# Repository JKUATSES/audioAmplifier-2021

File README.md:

# audioAmplifier-2021
This is a description of a simple audio amplifier design. The IC used is the TEA2025B and it is applied in bridge-tied mode for single speaker application.

<!--EQUALIZER_CIRCUITS-->
https://bestengineeringprojects.com/tone-control-circuit-active-and-passive/   <!-- primary source of LM741 equalizer/tonality control circuit -->
https://www.angelfire.com/electronic/funwithtubes/Amp-Tone-A.html
https://www.circuitstoday.com/passive-tone-control-circuit
https://learnabout-electronics.org/Amplifiers/amplifiers42.php

<!--PREAMPLIFIER_CIRCUITS-->
https://www.homemade-circuits.com/small-amplifier-circuit/
https://bestengineeringprojects.com/preamplifier-circuit/

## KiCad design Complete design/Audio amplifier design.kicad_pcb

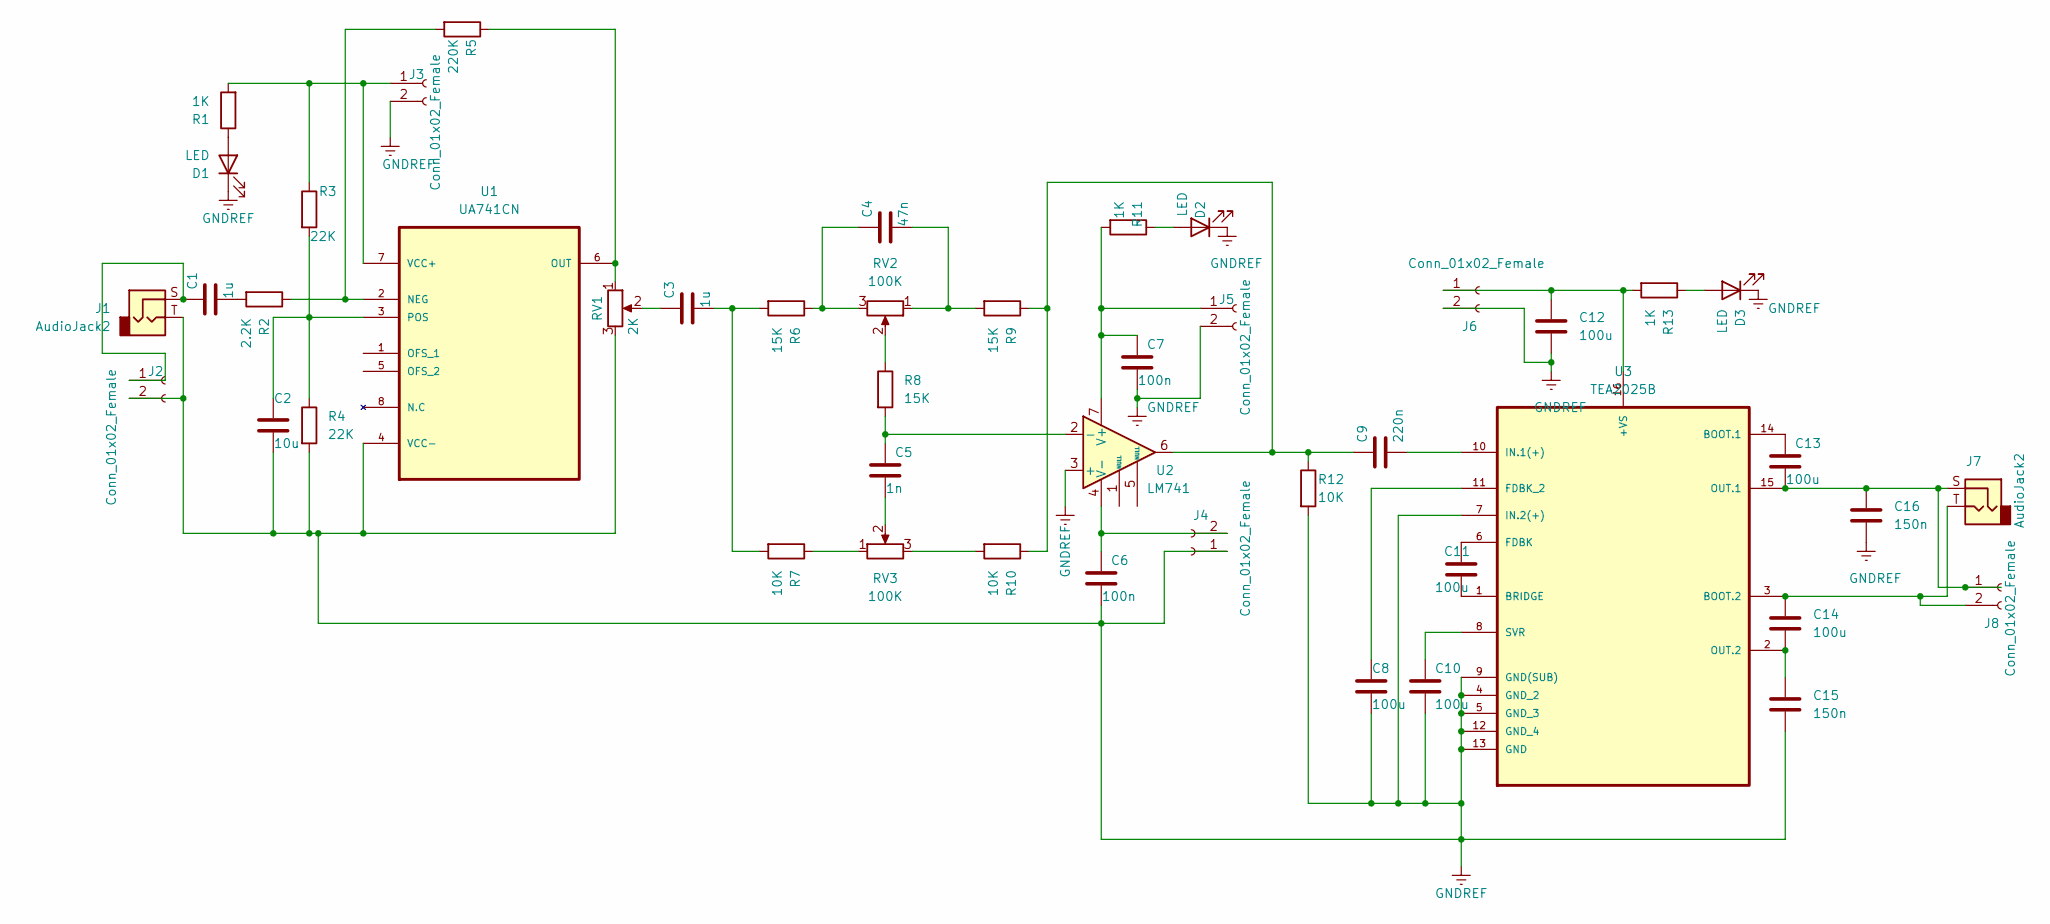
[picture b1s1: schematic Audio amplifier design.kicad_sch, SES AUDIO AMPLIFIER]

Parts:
C1, C3: 1u; CP_Radial_D5.0mm_P2.50mm
C2: 10u; CP_Radial_D5.0mm_P2.50mm
C4: 47n; CP_Radial_D5.0mm_P2.50mm
C5: 1n; CP_Radial_D5.0mm_P2.50mm
C6, C7: 100n; CP_Radial_D5.0mm_P2.50mm
C8, C10, C11, C12, C13, C14: 100u; CP_Radial_D5.0mm_P2.50mm
C9: 220n; CP_Radial_D5.0mm_P2.50mm
C15, C16: 150n; CP_Radial_D5.0mm_P2.50mm
D1, D2, D3: LED; LED_D5.0mm
J1, J7: AudioJack2; Jack_3.5mm_CUI_SJ1-3533NG_Horizontal
J2, J3, J4, J5, J6, J8: Conn_01x02_Female; TerminalBlock_4Ucon_1x02_P3.50mm_Vertical
R1, R11, R13: 1K; R_Axial_DIN0204_L3.6mm_D1.6mm_P7.62mm_Horizontal
R2: 2.2K; R_Axial_DIN0204_L3.6mm_D1.6mm_P7.62mm_Horizontal
R3, R4: 22K; R_Axial_DIN0204_L3.6mm_D1.6mm_P7.62mm_Horizontal
R5: 220K; R_Axial_DIN0204_L3.6mm_D1.6mm_P7.62mm_Horizontal
R6, R8, R9: 15K; R_Axial_DIN0204_L3.6mm_D1.6mm_P7.62mm_Horizontal
R7, R10, R12: 10K; R_Axial_DIN0204_L3.6mm_D1.6mm_P7.62mm_Horizontal
RV1: 2K; Potentiometer_ACP_CA9-H5_Horizontal
RV2, RV3: 100K; Potentiometer_ACP_CA9-H5_Horizontal
U1: UA741CN; DIP254P762X533-8; MPN UA741CN
U2: LM741; DIP254P762X533-8
U3: TEA2025B; DIP254P762X510-16; MPN TEA2025B

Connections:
GNDREF: C2.2, C6.2, C7.2, C8.2, C10.2, C12.2, C15.2, C16.2, D1.1 (K), D2.1 (K), D3.1 (K), J1.T, J2.2, J3.2, J4.1, J5.2, J6.2, R4.2, R12.2, RV1.3, U1.4 (VCC-), U2.3 (+), U3.4 (GND_2), U3.5 (GND_3), U3.7 (IN.2(+)), U3.9 (GND(SUB)), U3.12 (GND_4), U3.13 (GND)
unnamed: C1.1, J1.S, J2.1
unnamed: C1.2, R2.2
unnamed: C2.1, R3.2, R4.1, U1.3 (POS)
unnamed: C3.1, RV1.2
unnamed: C3.2, R6.2, R7.2
unnamed: C4.1, R6.1, RV2.3
unnamed: C4.2, R9.2, RV2.1
unnamed: C5.1, R8.2, U2.2 (-)
unnamed: C5.2, RV3.2
unnamed: C6.1, J4.2, U2.4 (V-)
unnamed: C7.1, J5.1, R11.2, U2.7 (V+)
unnamed: C8.1, U3.11 (FDBK_2)
unnamed: C9.1, R9.1, R10.1, R12.1, U2.6
unnamed: C9.2, U3.10 (IN.1(+))
unnamed: C10.1, U3.8 (SVR)
unnamed: C11.1, U3.6 (FDBK)
unnamed: C11.2, U3.1 (BRIDGE)
unnamed: C12.1, J6.1, R13.2, U3.16 (+VS)
unnamed: C13.1, U3.14 (BOOT.1)
unnamed: C13.2, C16.1, J7.S, J8.1, U3.15 (OUT.1)
unnamed: C14.1, J7.T, J8.2, U3.3 (BOOT.2)
unnamed: C14.2, C15.1, U3.2 (OUT.2)
unnamed: D1.2 (A), R1.1
unnamed: D2.2 (A), R11.1
unnamed: D3.2 (A), R13.1
unnamed: J3.1, R1.2, R3.1, U1.7 (VCC+)
unnamed: R2.1, R5.2, U1.2 (NEG)
unnamed: R5.1, RV1.1, U1.6 (OUT)
unnamed: R7.1, RV3.1
unnamed: R8.1, RV2.2
unnamed: R10.2, RV3.3

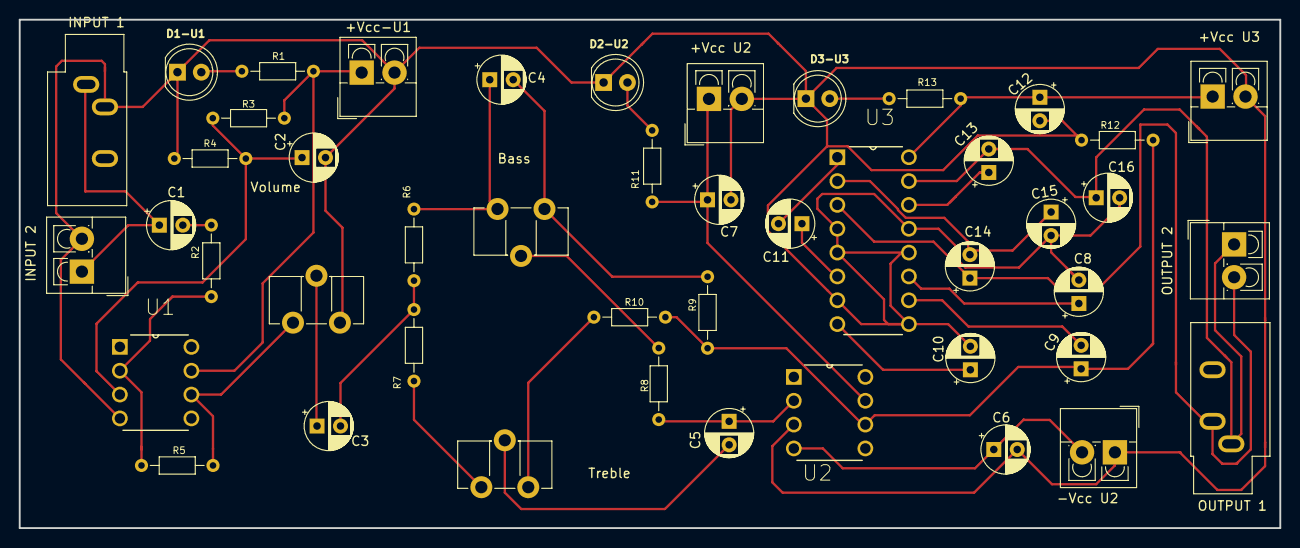
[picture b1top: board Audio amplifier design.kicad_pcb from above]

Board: 2 copper layers, 134.3 x 54.2 mm, 46 parts (0 on the bottom side), 32 nets.

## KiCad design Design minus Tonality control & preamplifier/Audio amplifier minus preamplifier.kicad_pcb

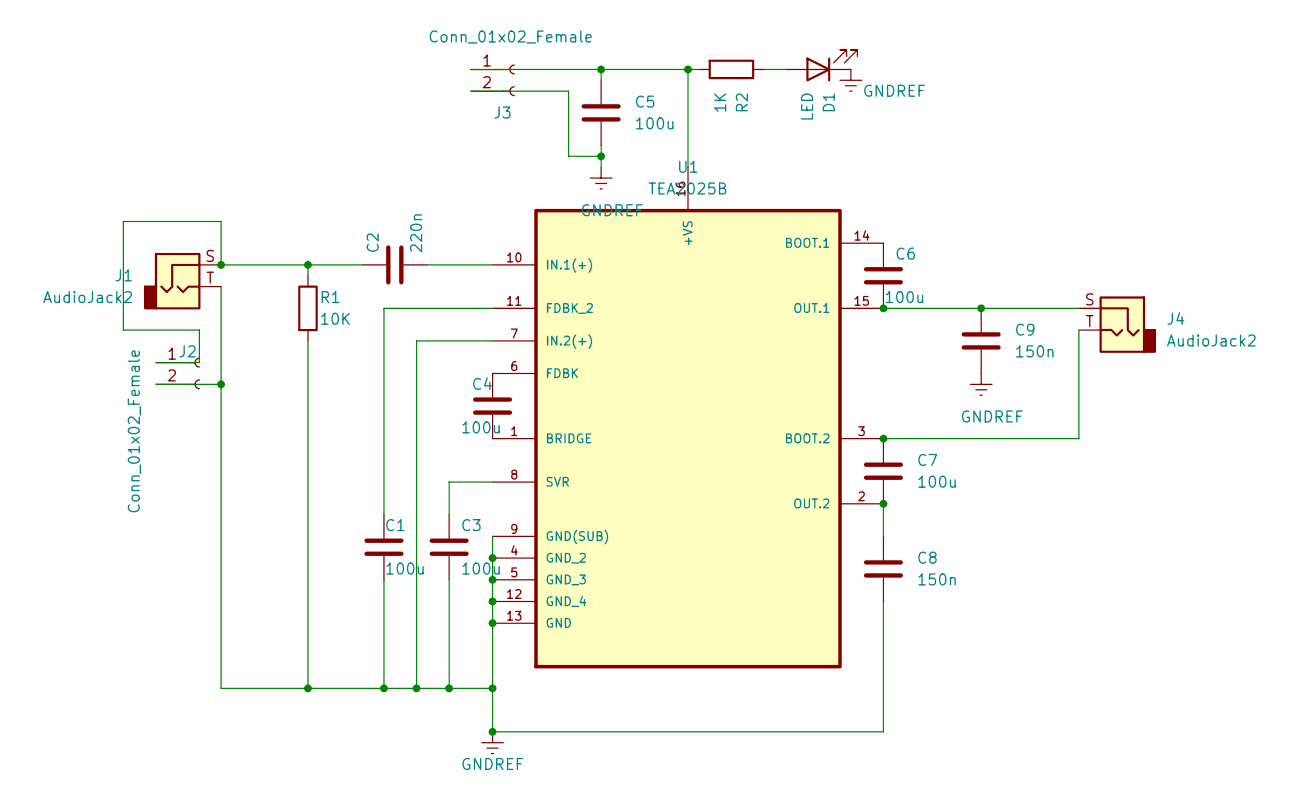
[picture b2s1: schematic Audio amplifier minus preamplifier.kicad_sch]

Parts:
C1, C3, C4, C5, C6, C7: 100u; CP_Radial_D5.0mm_P2.50mm
C2: 220n; CP_Radial_D5.0mm_P2.50mm
C8, C9: 150n; CP_Radial_D5.0mm_P2.50mm
D1: LED; LED_D5.0mm
J1, J4: AudioJack2; Jack_3.5mm_CUI_SJ-3523-SMT_Horizontal
J2, J3: Conn_01x02_Female; TerminalBlock_4Ucon_1x02_P3.50mm_Vertical
R1: 10K; R_Axial_DIN0204_L3.6mm_D1.6mm_P7.62mm_Horizontal
R2: 1K; R_Axial_DIN0204_L3.6mm_D1.6mm_P7.62mm_Horizontal
U1: TEA2025B; DIP254P762X510-16; MPN TEA2025B

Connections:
GNDREF: C1.2, C3.2, C5.2, C8.2, C9.2, D1.1 (K), J1.T, J2.2, J3.2, R1.2, U1.4 (GND_2), U1.5 (GND_3), U1.7 (IN.2(+)), U1.9 (GND(SUB)), U1.12 (GND_4), U1.13 (GND)
unnamed: C1.1, U1.11 (FDBK_2)
unnamed: C2.1, J1.S, J2.1, R1.1
unnamed: C2.2, U1.10 (IN.1(+))
unnamed: C3.1, U1.8 (SVR)
unnamed: C4.1, U1.6 (FDBK)
unnamed: C4.2, U1.1 (BRIDGE)
unnamed: C5.1, J3.1, R2.2, U1.16 (+VS)
unnamed: C6.1, U1.14 (BOOT.1)
unnamed: C6.2, C9.1, J4.S, U1.15 (OUT.1)
unnamed: C7.1, J4.T, U1.3 (BOOT.2)
unnamed: C7.2, C8.1, U1.2 (OUT.2)
unnamed: D1.2 (A), R2.1

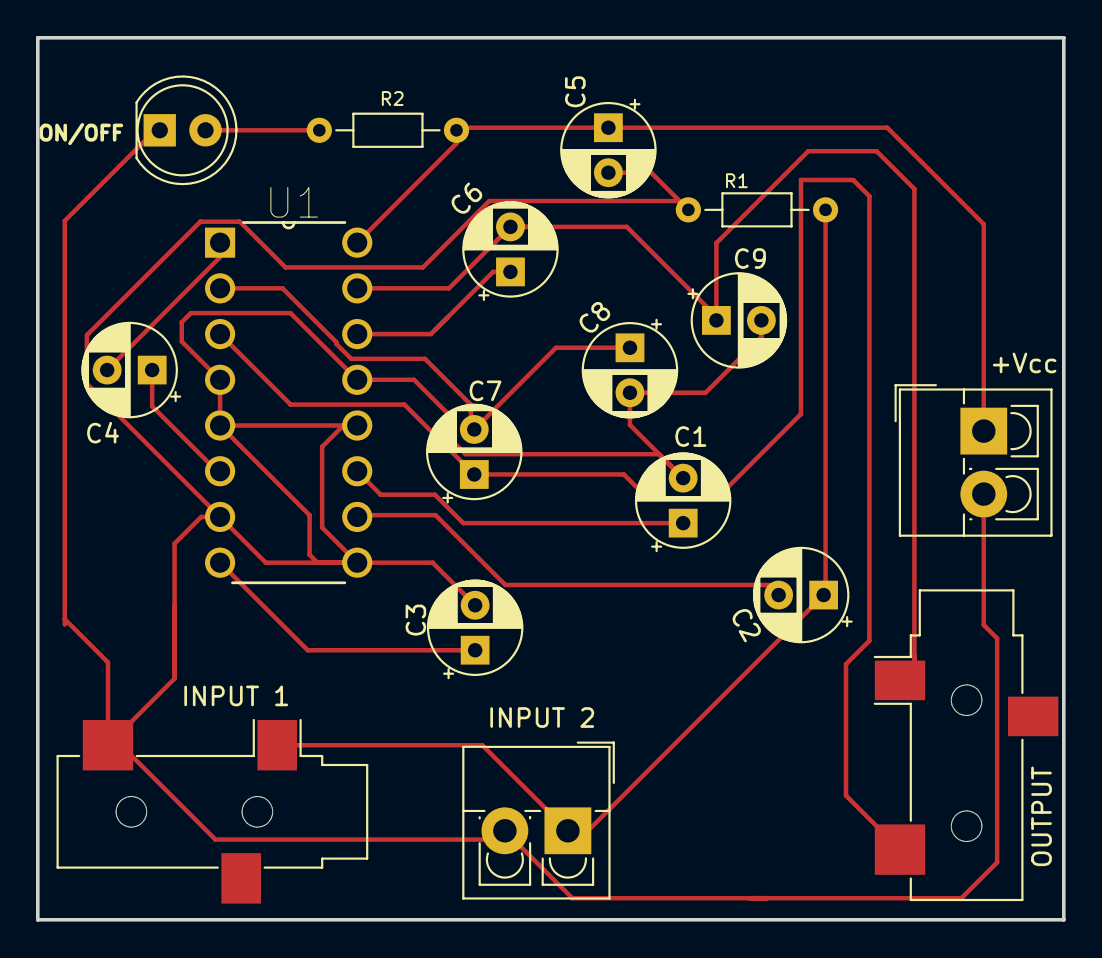
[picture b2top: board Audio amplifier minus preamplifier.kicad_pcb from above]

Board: 2 copper layers, 57.0 x 49.0 mm, 17 parts (0 on the bottom side), 13 nets.

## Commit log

2021-06-07 Audio amp 1
